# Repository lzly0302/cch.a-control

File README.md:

# CCH.a control

#### 介绍
{**以下是 Gitee 平台说明，您可以替换此简介**
Gitee 是 OSCHINA 推出的基于 Git 的代码托管平台（同时支持 SVN）。专为开发者提供稳定、高效、安全的云端软件开发协作平台
无论是个人、团队、或是企业，都能够用 Gitee 实现代码托管、项目管理、协作开发。企业项目请看 [https://gitee.com/enterprises](https://gitee.com/enterprises)}

#### 软件架构
软件架构说明

#### 安装教程

1.  xxxx
2.  xxxx
3.  xxxx

#### 使用说明

1.  xxxx
2.  xxxx
3.  xxxx

#### 参与贡献

1.  Fork 本仓库
2.  新建 Feat_xxx 分支
3.  提交代码
4.  新建 Pull Request

#### 特技

1.  使用 Readme\_XXX.md 来支持不同的语言，例如 Readme\_en.md, Readme\_zh.md
2.  Gitee 官方博客 [blog.gitee.com](https://blog.gitee.com)
3.  你可以 [https://gitee.com/explore](https://gitee.com/explore) 这个地址来了解 Gitee 上的优秀开源项目
4.  [GVP](https://gitee.com/gvp) 全称是 Gitee 最有价值开源项目，是综合评定出的优秀开源项目
5.  Gitee 官方提供的使用手册 [https://gitee.com/help](https://gitee.com/help)
6.  Gitee 封面人物是一档用来展示 Gitee 会员风采的栏目 [https://gitee.com/gitee-stars/](https://gitee.com/gitee-stars/)

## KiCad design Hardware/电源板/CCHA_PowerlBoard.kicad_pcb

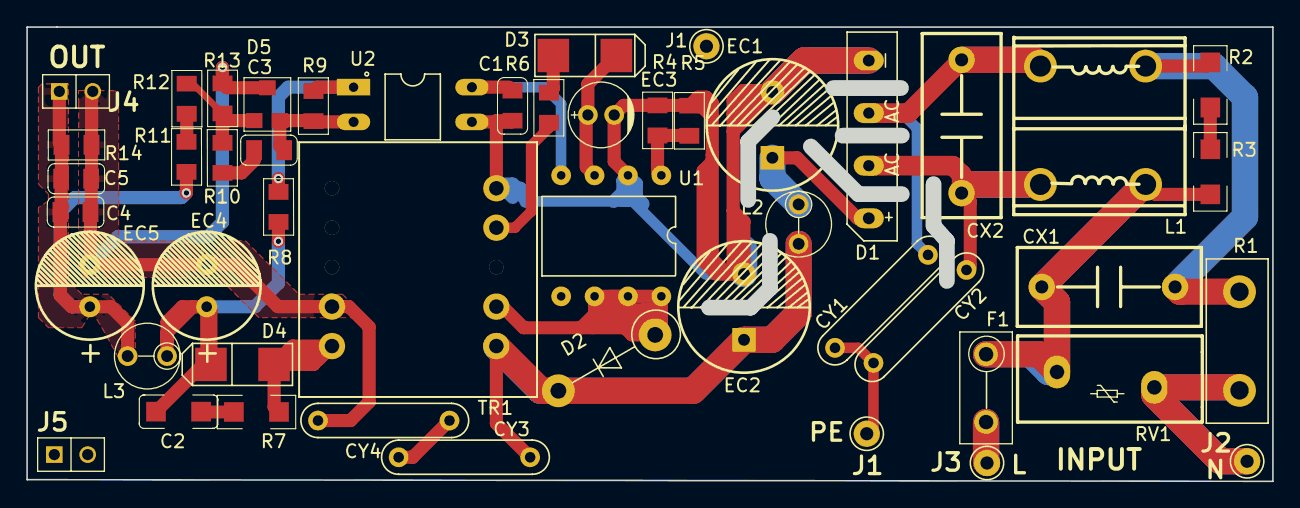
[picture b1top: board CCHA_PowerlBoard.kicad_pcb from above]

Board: 2 copper layers, 94.7 x 34.5 mm, 49 parts (0 on the bottom side), 28 nets.

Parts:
C1, C3: 1nF.0805; CAP.SMT.0805C
C2: 1nF.630V; CAP.SMT.1206C
C4: 1uF.0805; CAP.SMT.0805C
C5: 10nF.0805; CAP.SMT.0805C
CX1, CX2: 0.1uF.275V; CAP.DIP.X.0.1uF／275V
CY1, CY2: 102M.250V; CAP.DIP.Y.102M／250V
CY3, CY4: 222M.1KV; CAP.DIP.Y.102M／250V
D1: KBP310G; D.SMT.KBP310G
D2: D.DIP.PKC-136; D.DIP.PKC136.DO-41
D3: M7; D.SMT.1N5819.SMA
D4: SS520B; D.SMT.1N5819.SMA
D5: MMTL431A; BJT.SMT.SOT-23
EC1, EC2: 10uF.400V; CAP.DIP.10UF／400V.10X15
EC3: 10uF.50V; CAP.DIP.10uF／50V.5.2X11.6
EC4, EC5: 330uF.25V; CAP.DIP.330uF／25V.8X12
F1: 10R_2W; FUSE.3.15A
J1, J1#2: PE; CON_DIP_1X1PIN
J2: N; CON_DIP_1X1PIN
J3: L; CON_DIP_1X1PIN
J4, J5: 1X2P.2.54MM; CON_DIP_1X2PIN_2.54MM
L1: 22mH.UU9.8; L.DIP.JF1058T-3.5MH
L2: 1mH; L.PID.2.2mH
L3: 3.3uH/1A; L.PID.2.2mH
R1: RES.NTC.5D-13; FUSE.DIP.10D-9
R2, R3: 1M.1206; RES.SMT.1206
R4, R5: 2R7.0805; RES.SMT.0805
R6: 6R8.0805; RES.SMT.0805
R7: 47R.1206; RES.SMT.1206
R8, R9: 1k.0805; RES.SMT.0805
R10: 4.7k.0805; RES.SMT.0805
R11: 20k.0805; RES.SMT.0805
R12: 18k.0805; RES.SMT.0805
R13, R14: 10k.0805; RES.SMT.0805
RV1: TDK471KD14; RES.DIP.RV.TDK471KD14
TR1: EE19.PN6047.9W; L_TRANS_DIP_EE19_PN6047_9W
U1: PN6047H.SOP-8; IC_DIP-8-PN6047
U2: PC817B; OPTO.DIP.PC817B

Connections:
+12VA: C4.1, C5.1, EC5.1, J4.1, L3.2, R11.1, R14.1
/AC_L: F1.1, J3.1
/AC_N: J2.1, R1.1, RV1.1
/PE: CY1.1, CY2.2, J1#2.1
GNDA: C4.2, C5.2, CY4.1, D5.3, EC4.2, EC5.2, J4.2, R13.2, R14.2, TR1.9
GNDD: C1.2, D1.4, EC1.2, EC2.2, EC3.2, R4.2, R5.2, TR1.5, U1.2, U2.3
unnamed: C1.1, U1.4, U2.4
unnamed: C2.1, D4.1, EC4.1, L3.1, R8.1
unnamed: C2.2, R7.1
unnamed: C3.1, D5.2, R9.2, U2.2
unnamed: C3.2, R10.2
unnamed: CX1.1, F1.2, L1.2, R3.1, RV1.2
unnamed: CX1.2, L1.1, R1.2, R2.2
unnamed: CX2.1, CY2.1, D1.2, L1.3
unnamed: CX2.2, CY1.2, D1.1, L1.4
unnamed: CY3.1, CY4.2
unnamed: CY3.2, D2.1, EC2.1, L2.2, TR1.1
unnamed: D1.3, EC1.1, L2.1
unnamed: D2.2, TR1.2, U1.6, U1.7, U1.8
unnamed: D3.1, EC3.1, U1.3
unnamed: D3.2, R6.1
unnamed: D4.2, R7.2, TR1.10
unnamed: D5.1, R10.1, R12.2, R13.1
unnamed: R2.1, R3.2
unnamed: R4.1, R5.1, U1.1
unnamed: R6.2, TR1.4
unnamed: R8.2, R9.1, U2.1
unnamed: R11.2, R12.1

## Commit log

2021-06-24 上传输配控制站CCHA原理图及PCB
2021-06-24 修改铺铜设置及原理图元器件位置修改
2021-06-24 修改原理图参数
2021-07-02 工程建立
2021-07-07 底层驱动配置
2021-07-08 提交可编译版本
2021-07-10 硬件测试基本正常，对等链路还需调试
2021-07-14 串口调试可用
2021-07-14 提交本地文件
2021-07-20 存储模块移植完毕
2021-07-23 调整串口底层驱动
2021-07-29 增加boot文件，合并文件调试初步完成
2021-08-05 增加升级分发任务，待调试
2021-08-09 增加除湿模块程序升级分发
2021-08-10 优化升级分发模块
2021-08-12 增加远程控制寄存器
2021-08-23 加入主站功能
2021-08-26 将除湿模块数据点独立出来
2021-08-26 增加除湿模块接口
2021-08-26 待调试版本
2021-08-27 除湿模块链路基本可用
2021-08-28 除湿模块寄存器独立地址分配
2021-08-30 增加同步数据
2021-08-31 优化同步逻辑
2021-09-11 增加文档
2021-09-14 文件补齐
2021-09-16 调整接口位置
2021-09-18 加入除湿模块数据点
2021-09-18 加入除湿模块测试点，待测试
2021-09-23 调试版本
2021-09-24 除湿模块通信数据基本完成，待测试
